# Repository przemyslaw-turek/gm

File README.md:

# GRANDMA MONITOR - electronic part

## I. Description
<OL>
<P style="line-height: 1cm; ">Grandma monitor is a system created to monitor conditions inside of old person's flat.
The system uses diffrent sensors to collect informations about movement, temperature etc. and send it via internet to protector. 
Main controler (Raspberry Pi 3) is connected with big red button, which turn on panic alarm (on protectors mobile device).
Except Raspberry Pi we use also ESP8266 which supports whireless communication and enables placement of sensors in the other part of the flat. </P>
</P>
<P style="line-height: 1cm; ">Befor you begin instalation you need to decide which sensors you want to use and where to put them.
Here is the list of the sensors that we support:</P>
<LI> MQ-2 Semiconductor Sensor for Combustible Gas  </LI>
<LI> PIR HC-SR501 Motion Sensor </LI>
<LI> DS18B20 Temperature Sensor </LI>
<LI> DHT11 Humidity & Temperature Sensor</LI>
<LI> Reed relay</LI>
</OL>

## II. Instalation
<OL>
<P style="line-height: 1cm; ">
The electronic part of the project is divided into three main parts:
</P>
<LI> Raspberry PI 3	(master controller) </LI>
<LI> ESP8266	(slave controller) </LI>
<LI> Sensors </LI>
<P style="line-height: 1cm; ">

</P>
<P style="line-height: 1cm; ">
In each of this parts you can find the manual.
</P>

</OL>

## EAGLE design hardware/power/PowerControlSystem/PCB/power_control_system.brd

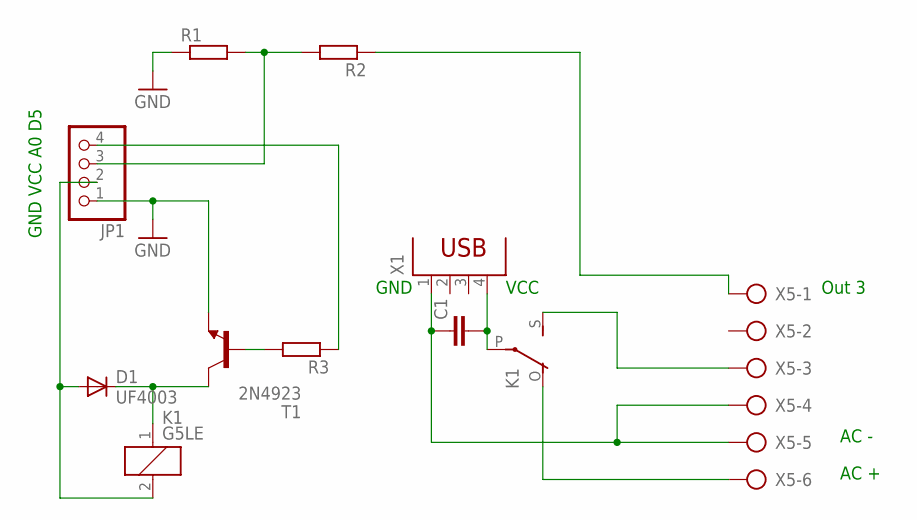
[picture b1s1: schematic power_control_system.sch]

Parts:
C1: C2,5-3; C2.5-3
D1: UF4003; DO41-10
JP1: PINHD-1X4; 1X04
K1: G5LE
R1, R2, R3: R-EU_0204/2V; 0204V
T1: 2N4923; TO126
X1: PN87520
X5: AK300/6

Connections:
GND: JP1.1, R1.1, T1.1 (E)
unnamed: JP1.3, R1.2, R2.2
unnamed: JP1.4, R3.1
unnamed: R3.2, T1.3 (B)
unnamed: D1.C, K1.1, T1.2 (C)
unnamed: D1.A, JP1.2, K1.2
unnamed: C1.1, X1.1, X5.4, X5.5
unnamed: C1.2, K1.P, X1.4
unnamed: K1.O, X5.6
unnamed: K1.S, X5.3
unnamed: R2.1, X5.1

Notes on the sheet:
GND VCC A0 D5
GND
VCC
AC +
AC -
Out 3

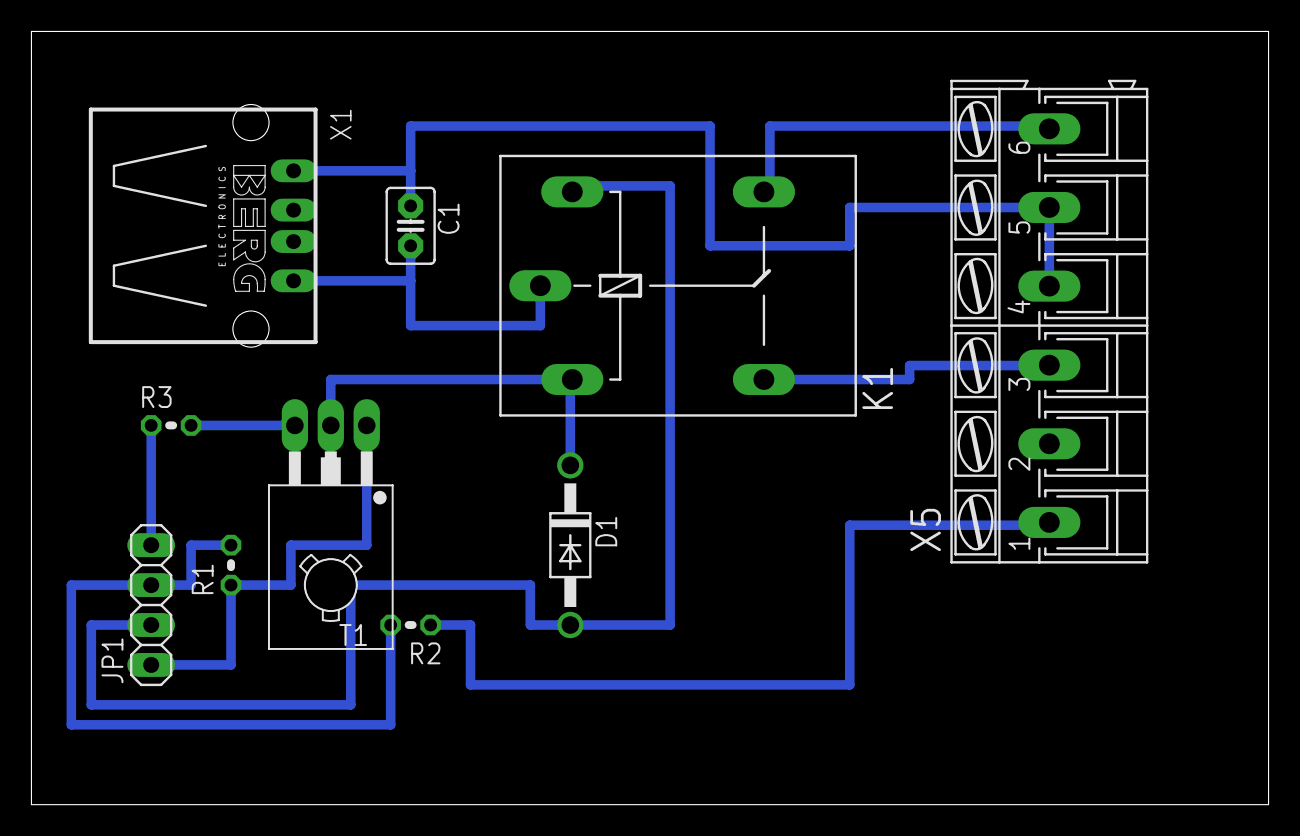
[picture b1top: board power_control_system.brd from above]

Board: 2 copper layers, 78.7 x 49.2 mm, 10 parts (0 on the bottom side), 11 nets.

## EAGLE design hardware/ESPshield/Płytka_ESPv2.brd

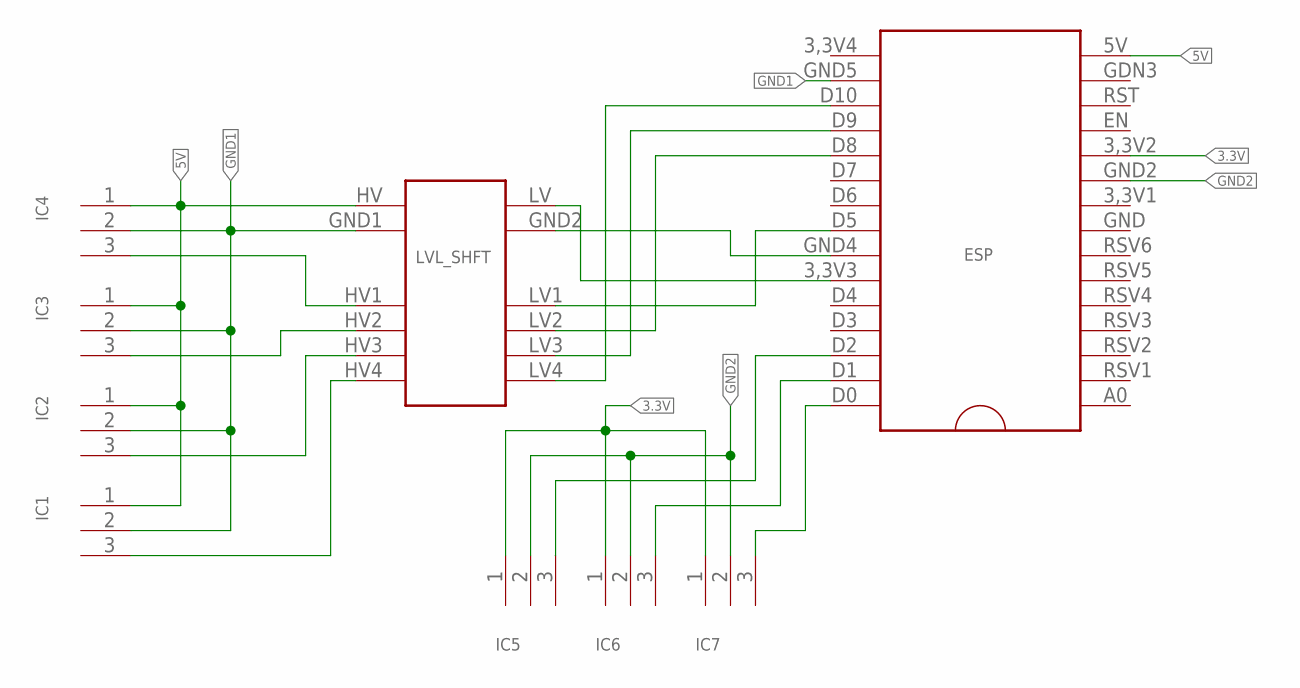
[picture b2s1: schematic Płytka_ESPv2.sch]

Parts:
ESP: ESP8266_NODEMCUV2; ESP8266_NODEMCV2
IC1, IC2, IC3, IC4, IC5, IC6, IC7: 3,5MM_3PIN
LVL_SHFT: LVL_SHIFTER_4CH

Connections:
3.3V: ESP.3,3V2, IC5.1, IC6.1, IC7.1
5V: ESP.5V, IC1.1, IC2.1, IC3.1, IC4.1, LVL_SHFT.HV
GND1: ESP.GND5, IC1.2, IC2.2, IC3.2, IC4.2, LVL_SHFT.GND1
GND2: ESP.GND2, IC5.2, IC6.2, IC7.2
unnamed: IC4.3, LVL_SHFT.HV1
unnamed: IC3.3, LVL_SHFT.HV2
unnamed: IC2.3, LVL_SHFT.HV3
unnamed: IC1.3, LVL_SHFT.HV4
unnamed: ESP.D5, LVL_SHFT.LV1
unnamed: ESP.D8, LVL_SHFT.LV2
unnamed: ESP.D9, LVL_SHFT.LV3
unnamed: ESP.D0, IC7.3
unnamed: ESP.GND4, LVL_SHFT.GND2
unnamed: ESP.D10, LVL_SHFT.LV4
unnamed: ESP.3,3V3, LVL_SHFT.LV
unnamed: ESP.D2, IC5.3
unnamed: ESP.D1, IC6.3

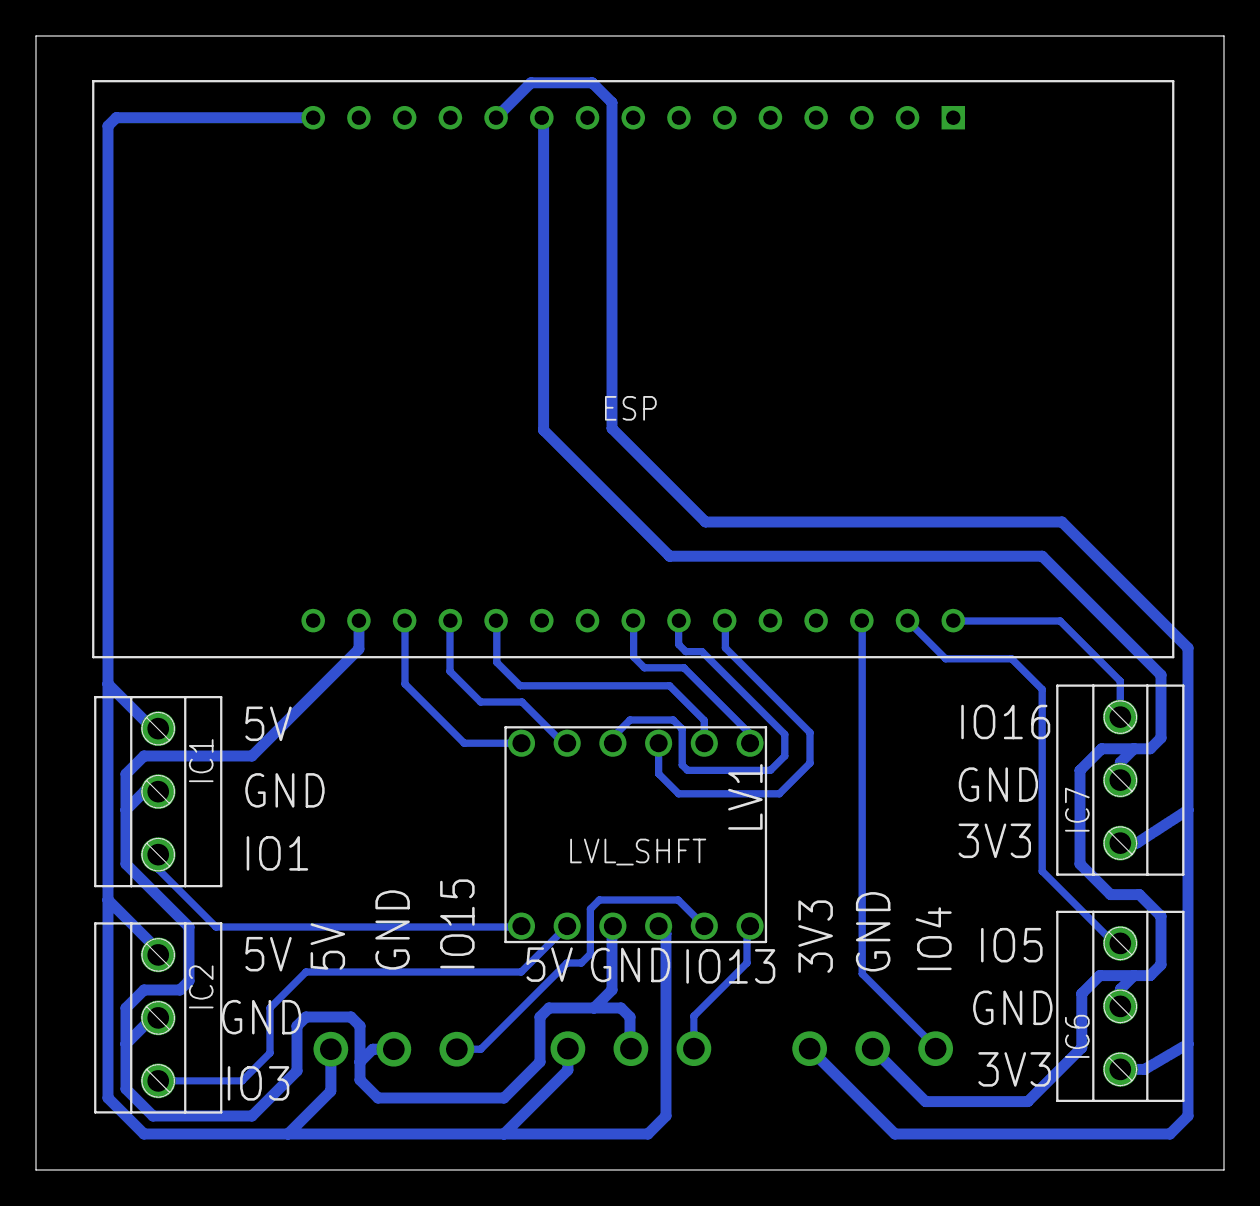
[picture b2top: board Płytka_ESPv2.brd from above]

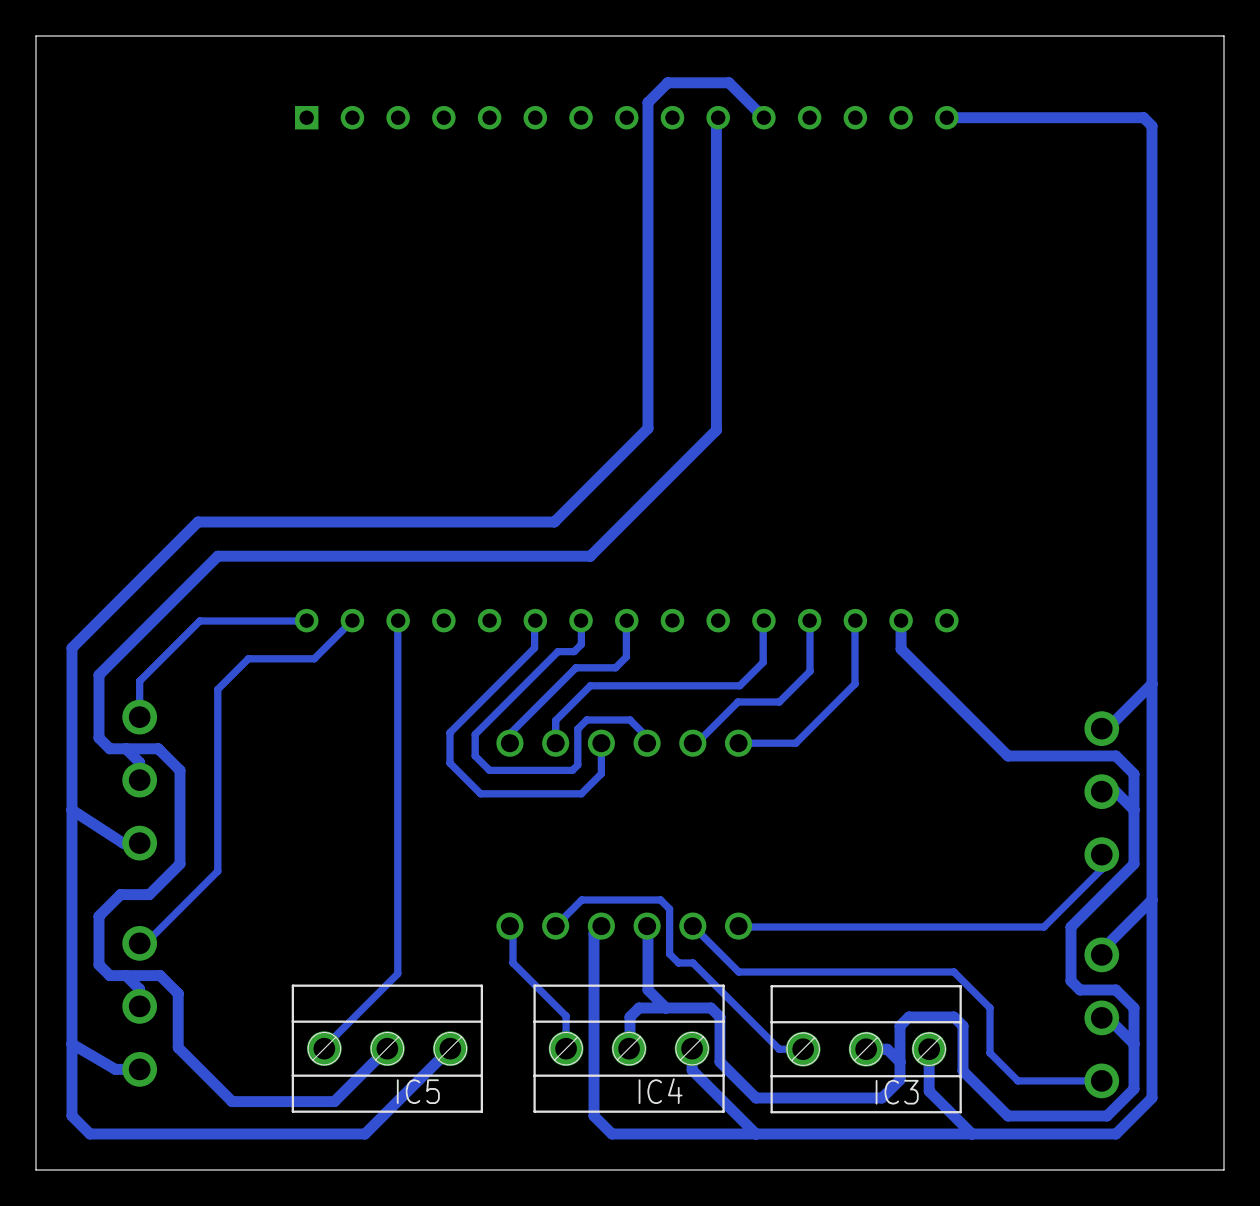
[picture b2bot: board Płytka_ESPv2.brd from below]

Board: 2 copper layers, 66.0 x 63.0 mm, 9 parts (3 on the bottom side), 17 nets.

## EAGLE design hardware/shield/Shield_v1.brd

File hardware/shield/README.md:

<b>Raspberry Pi 3 Shield</font></b><br />
<br />
I. BASIC VERSION:
<br />
<br />
Necessery elements:
<br />
<ul>
<li>7x Screw terminals 3-Pin 3,5mm - https://botland.com.pl/zlacza-ark/2555-zlacze-ark-raster-35-mm-3-pin-.html</li>
<br />
<li>Female goldpin header 2x40 2,54mm - https://botland.com.pl/gniazda-szpilkowe-goldpin/1104-listwa-zeska-2x40.html</li>
<br />
<li>Level shifter - http://allegro.pl/modul-konwerter-poziomow-3-3v-5v-stanow-log-i4973044836.html</li>
<br />
</ul>

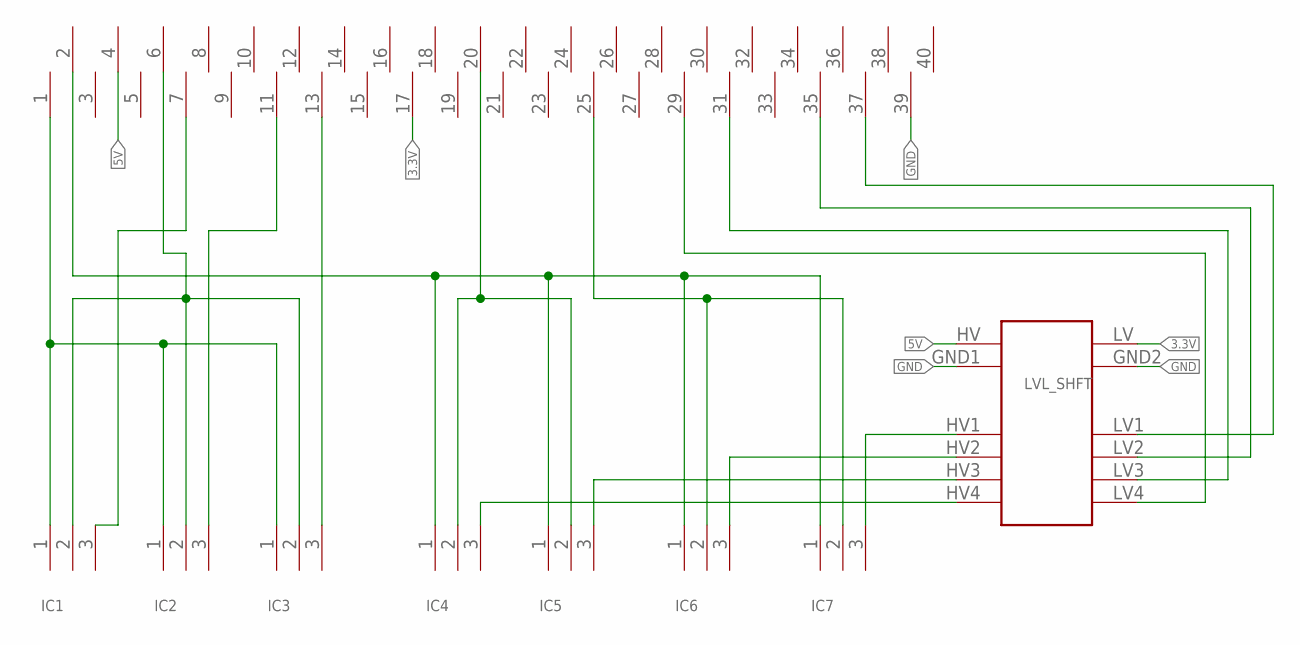
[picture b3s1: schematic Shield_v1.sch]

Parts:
IC1, IC2, IC3, IC4, IC5, IC6, IC7: 3,5MM_3PIN
IC17: 40_PIN_2.54MM
LVL_SHFT: LVL_SHIFTER_4CH

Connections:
3.3V: IC17.17, LVL_SHFT.LV
5V: IC17.4, LVL_SHFT.HV
GND: IC17.39, LVL_SHFT.GND1, LVL_SHFT.GND2
unnamed: IC1.1, IC2.1, IC3.1, IC17.1
unnamed: IC4.1, IC5.1, IC6.1, IC7.1, IC17.2
unnamed: IC1.2, IC2.2, IC3.2, IC17.6
unnamed: IC4.2, IC5.2, IC17.20
unnamed: IC6.2, IC7.2, IC17.25
unnamed: IC7.3, LVL_SHFT.HV1
unnamed: IC6.3, LVL_SHFT.HV2
unnamed: IC5.3, LVL_SHFT.HV3
unnamed: IC4.3, LVL_SHFT.HV4
unnamed: IC17.37, LVL_SHFT.LV1
unnamed: IC17.35, LVL_SHFT.LV2
unnamed: IC17.31, LVL_SHFT.LV3
unnamed: IC17.29, LVL_SHFT.LV4
unnamed: IC1.3, IC17.7
unnamed: IC2.3, IC17.11
unnamed: IC3.3, IC17.13

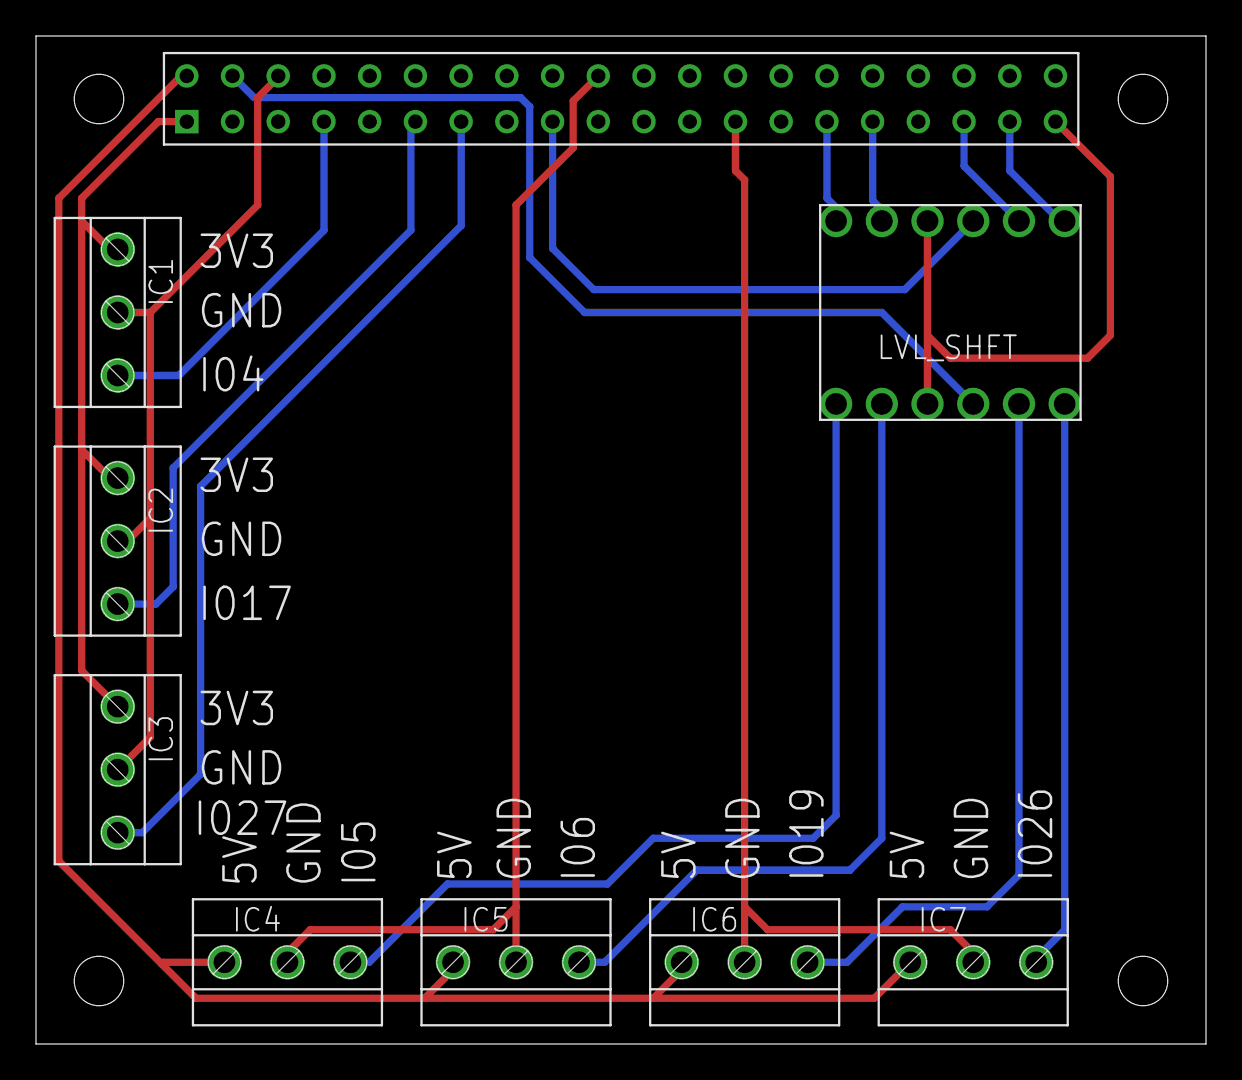
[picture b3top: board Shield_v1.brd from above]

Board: 2 copper layers, 65.0 x 56.0 mm, 9 parts (0 on the bottom side), 19 nets.

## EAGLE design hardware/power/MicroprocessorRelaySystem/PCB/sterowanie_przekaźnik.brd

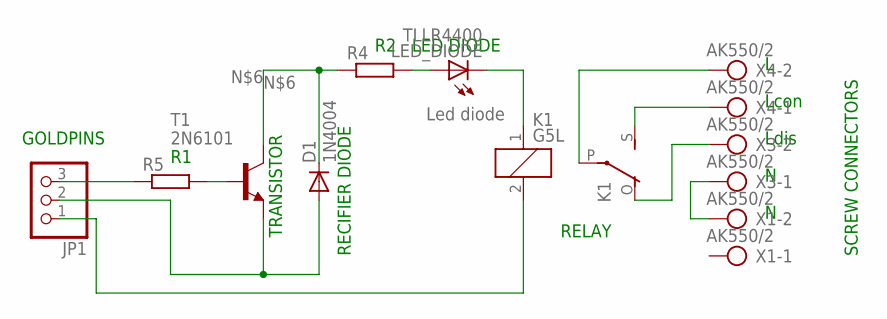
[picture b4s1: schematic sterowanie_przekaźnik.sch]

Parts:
D1: 1N4004; DO41-10
JP1: PINHD-1X3; 1X03
K1: G5L; G5LE
LED_DIODE: TLLR4400; LED3MM
R4, R5: R0207/10; 0207/10
T1: 2N6101; TO220
X1, X3, X4: AK550/2

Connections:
unnamed: K1.P, X4.2
unnamed: K1.S, X4.1
unnamed: X1.2, X3.1
unnamed 3: K1.1, LED_DIODE.K (C); also elsewhere on the board
unnamed: JP1.3, R5.1
unnamed: D1.C, R4.1, T1.2 (C)
unnamed: D1.A, JP1.2, T1.3 (E)
unnamed: K1.O, X3.2
unnamed: JP1.1, K1.2
unnamed: R5.2, T1.1 (B)
unnamed 10: LED_DIODE.A, R4.2; also elsewhere on the board

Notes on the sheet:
RECIFIER DIODE
GOLDPINS
LED DIODE
TRANSISTOR
RELAY
SCREW CONNECTORS
Lcon
Ldis

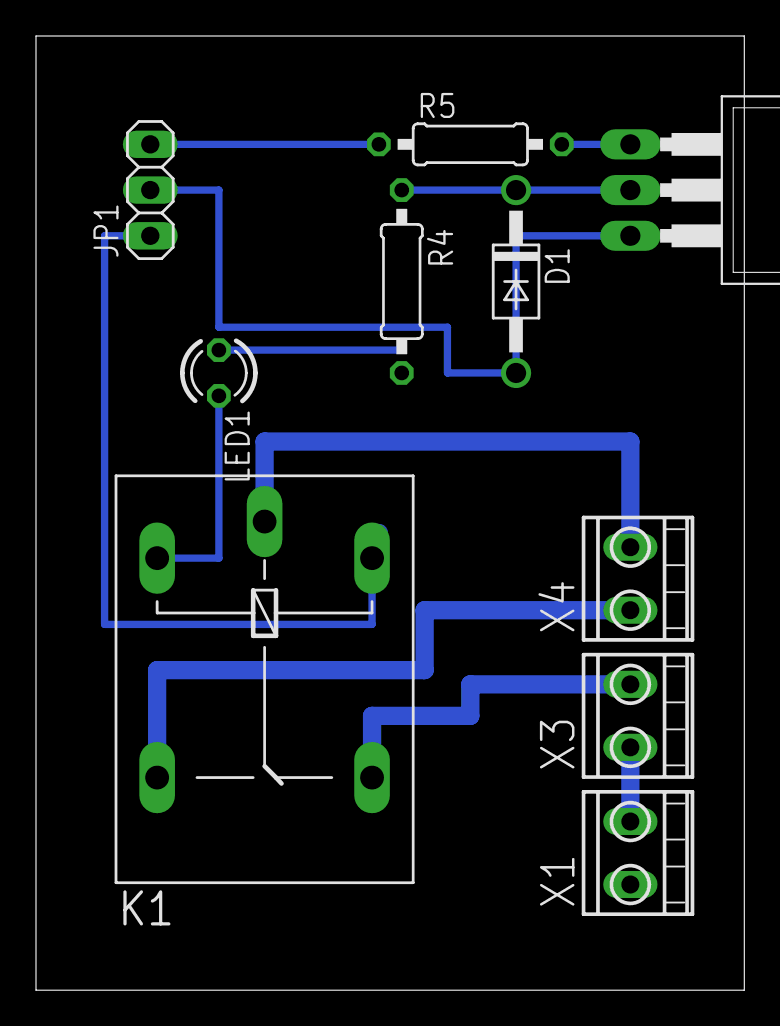
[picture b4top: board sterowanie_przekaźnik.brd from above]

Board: 2 copper layers, 39.4 x 53.0 mm, 10 parts (0 on the bottom side), 11 nets.

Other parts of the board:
LED1: TLLR4400; LED3MM

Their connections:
unnamed 3: LED1.K; also elsewhere on the board
unnamed 10: LED1.A; also elsewhere on the board

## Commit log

2016-11-18 Folder structure
2016-11-25 Configuration file for Home Assistant
2016-11-28 .gitignore added
2016-11-28 PCB shield schematic for Raspberry Pi 3
2016-11-28 Raspberry Pi 3 gpio pinout
2016-11-28 Raspberry Pi 3 gpio pinout new version
2016-11-29 Python script
2016-11-29 Big red button Python script
2016-11-29 script
2016-11-29 configuration.yaml
2016-11-29 buttonscript
2016-11-29 Raspbian's installation - picture of Rufus
2016-11-29 Raspbian's installation - pictrue of Putty
2016-11-29 Raspbian's installation
2016-11-30 ESP8266 configuration, code connecting to raspberry using wifi and mqtt
2016-11-30 DHT11 temperature and humidity sensor code
2016-11-30 Delete PCBv2.pdf
    Update to newer version
2016-11-30 Motion sensor - schematic
2016-11-30 Movement of files
2016-11-30 new catalogs
2016-12-01 New folders
2016-12-01 Home Assistant's configuration
2016-12-01 Remove the file
2016-12-01 Removing the file
2016-12-01 Home Assistant's main page
2016-12-01 I add password to mqtt
2016-12-01 HTML correction
2016-12-04 screen
2016-12-05 Configuration.yaml - localhost
2016-12-05 New Python's script and configuration.yaml
2016-12-05 New buttonscript's version
2016-12-08 sensors
2016-12-08 Raspberry Pi 3 shield
2016-12-08 Description for Raspberry Pi 3 shield
2016-12-08 Sensors' schematic
2016-12-08 Removing old files
2016-12-14 New configuration.yaml
2016-12-14 Add description
2017-01-06 Add files via upload
    Bash script which is meant to install both mqtt and homeassistant. When using this you can skip whole installation. You can use this only after you are done with Raspbian configuration.
    To run simply navigate in terminal to skrypt.sh on your Raspberry PI and type "sudo bash skrypt.sh" After this you should have mqtt and homeassistant installed. Use readme to verify if everything was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
2017-01-11 Create ssh file to enable connecting via putty.
2017-01-19 photo
2017-06-05 Kuba's innovations
2017-06-05 Kuba's file
2017-06-06 Kuba's things
2017-06-06 Rafal's shields
2017-06-11 ESP code ver 2
2017-06-11 shield's update
2017-06-11 ESP shield v2
2017-06-11 shield v2
2017-06-23 ESPv3 shield
2017-07-09 ESP libraries
2017-07-10 MQ2 and motion sensor message changed to "triggered"
2017-07-10 After disarming the alarm goes to "armed_home" state
2017-07-10 Libraries for ESP ver 2
2017-07-16 Files with scheme and PCB board for RPi shield
2017-07-16 Files with scheme and PCB board for ESP8266
2017-07-18 Create box
